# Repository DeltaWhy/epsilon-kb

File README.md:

# epsilon-kb
A little 10-key keyboard for ASETNIOP

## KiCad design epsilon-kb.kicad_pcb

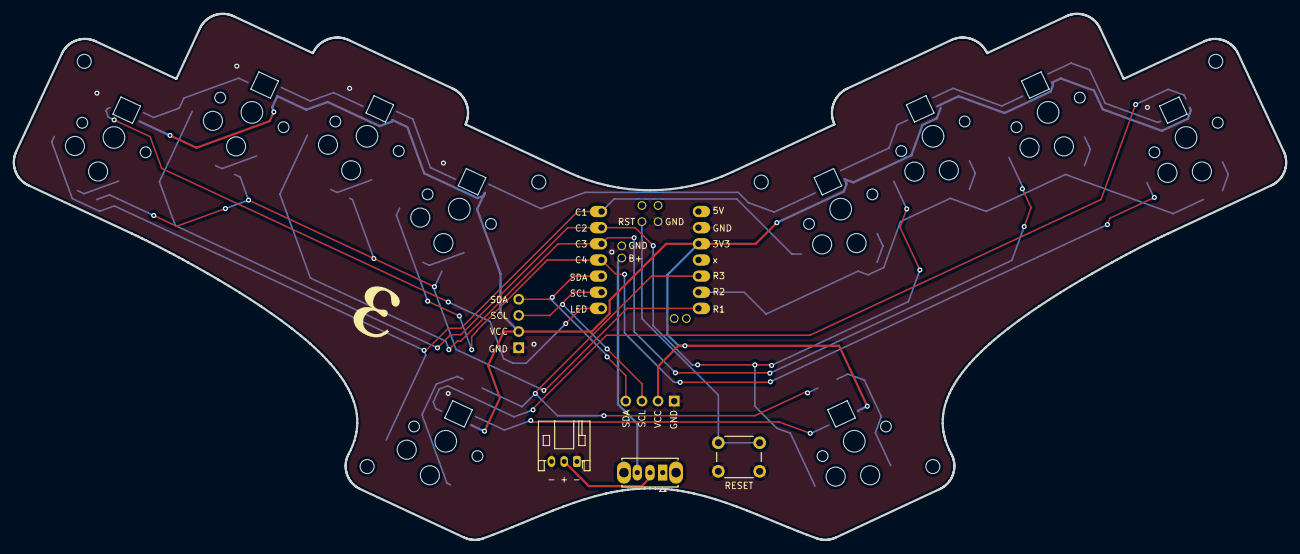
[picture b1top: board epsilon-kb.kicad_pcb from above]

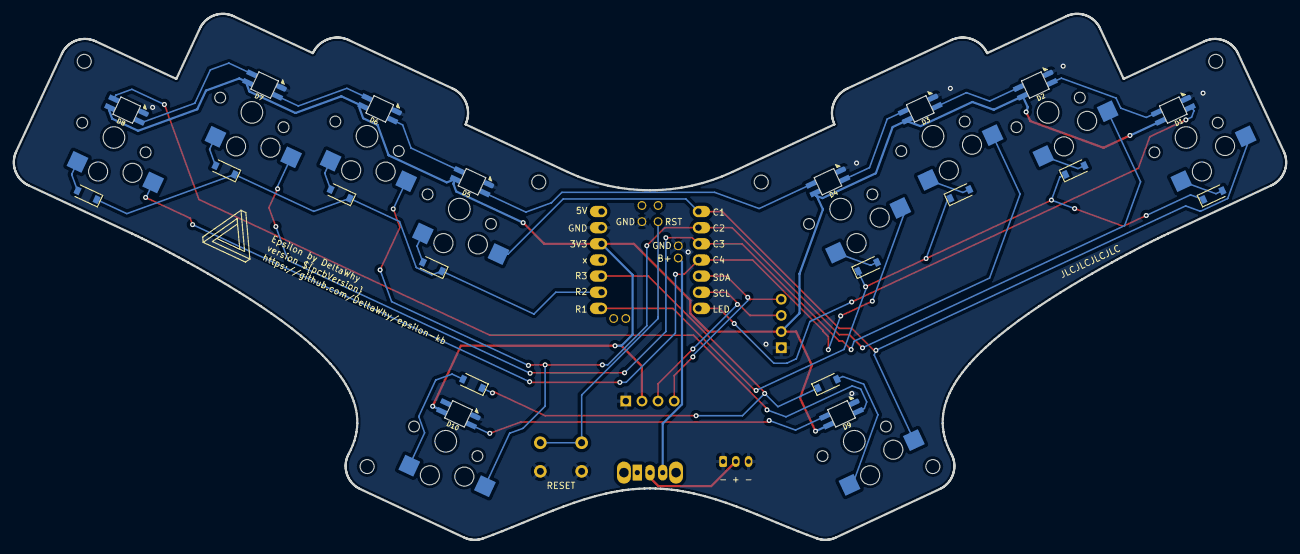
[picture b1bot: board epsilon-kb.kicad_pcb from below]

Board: 2 copper layers, 200.2 x 82.7 mm, 36 parts (20 on the bottom side), 34 nets.

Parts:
BT1: Battery; JST_PH_S3B-PH-K_1x03_P2.00mm_Horizontal
D1, D2, D3, D4, D5, D6, D7, D8, D9, D10: SK6812MINI-E; SK6812-MINI-E
D11, D12, D13, D14, D15, D16, D17, D18, D19, D20: 1N4148W; D_SOD-123
J1: OLED-128x64
J2: OLED-128x32; OLED-128x32-cutout
SW1, SW2, SW3, SW4, SW5, SW6, SW7, SW8, SW9, SW10: SW_Push; pg1350-H
SW11: SW_SPDT; SW_Slide_1P2T_CK_OS102011MS2Q
SW12: SW_Push; SW_PUSH_6mm
U1: xiao-ble; xiao-ble-tht

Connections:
+3V3: D1.1 (VDD), D2.1 (VDD), D3.1 (VDD), D4.1 (VDD), D5.1 (VDD), D6.1 (VDD), D7.1 (VDD), D8.1 (VDD), D9.1 (VDD), D10.1 (VDD), J1.2 (VCC), J2.2 (VCC), U1.12 (3V3)
+BATT: SW11.3 (C), U1.19 (BAT)
/B+: BT1.2, SW11.2 (B)
/LED_IN: D1.4 (DIN), U1.7 (B8_TX/1.11)
/RST: SW12.1, U1.17 (RESET)
/SCL: J1.3 (SCL), J2.3 (SCL), U1.6 (A9_SCL/0.05_H)
/SDA: J1.4 (SDA), J2.4 (SDA), U1.5 (A8_SDA/0.04_H)
C1: SW1.2, SW5.2, SW9.2, U1.1 (A2/0.02_H)
C2: SW2.2, SW6.2, SW10.2, U1.2 (A4/0.03_H)
C3: SW3.2, SW7.2, U1.3 (A10/0.28)
C4: SW4.2, SW8.2, U1.4 (A11/0.29)
GND: BT1.1, BT1.3, D1.3 (VSS), D2.3 (VSS), D3.3 (VSS), D4.3 (VSS), D5.3 (VSS), D6.3 (VSS), D7.3 (VSS), D8.3 (VSS), D9.3 (VSS), D10.3 (VSS), J1.1 (GND), J2.1 (GND), SW12.2, U1.13 (GND), U1.18 (GND), U1.20 (GND)
unnamed: D1.2 (DOUT), D2.4 (DIN)
unnamed: D2.2 (DOUT), D3.4 (DIN)
unnamed: D3.2 (DOUT), D4.4 (DIN)
unnamed: D4.2 (DOUT), D5.4 (DIN)
unnamed: D5.2 (DOUT), D6.4 (DIN)
unnamed: D6.2 (DOUT), D7.4 (DIN)
unnamed: D7.2 (DOUT), D8.4 (DIN)
unnamed: D8.2 (DOUT), D9.4 (DIN)
unnamed: D9.2 (DOUT), D10.4 (DIN)
unnamed: D11.2 (A), SW1.1
unnamed: D12.2 (A), SW2.1
unnamed: D13.2 (A), SW3.1
unnamed: D14.2 (A), SW4.1
unnamed: D15.2 (A), SW5.1
unnamed: D16.2 (A), SW6.1
unnamed: D17.2 (A), SW7.1
unnamed: D18.2 (A), SW8.1
unnamed: D19.2 (A), SW9.1
unnamed: D20.2 (A), SW10.1
R1: D11.1 (K), D12.1 (K), D13.1 (K), D14.1 (K), U1.8 (B9_RX/1.12)
R2: D15.1 (K), D16.1 (K), D17.1 (K), D18.1 (K), U1.9 (A7_SCK/1.13)
R3: D19.1 (K), D20.1 (K), U1.10 (A5_MISO/1.14)

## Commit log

2023-01-14 Schematic
2023-06-04 add Makefile and images
2023-06-04 render only visible gerber layers
